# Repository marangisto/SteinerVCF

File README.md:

# SteinerVCF
Steiner VCF Replica

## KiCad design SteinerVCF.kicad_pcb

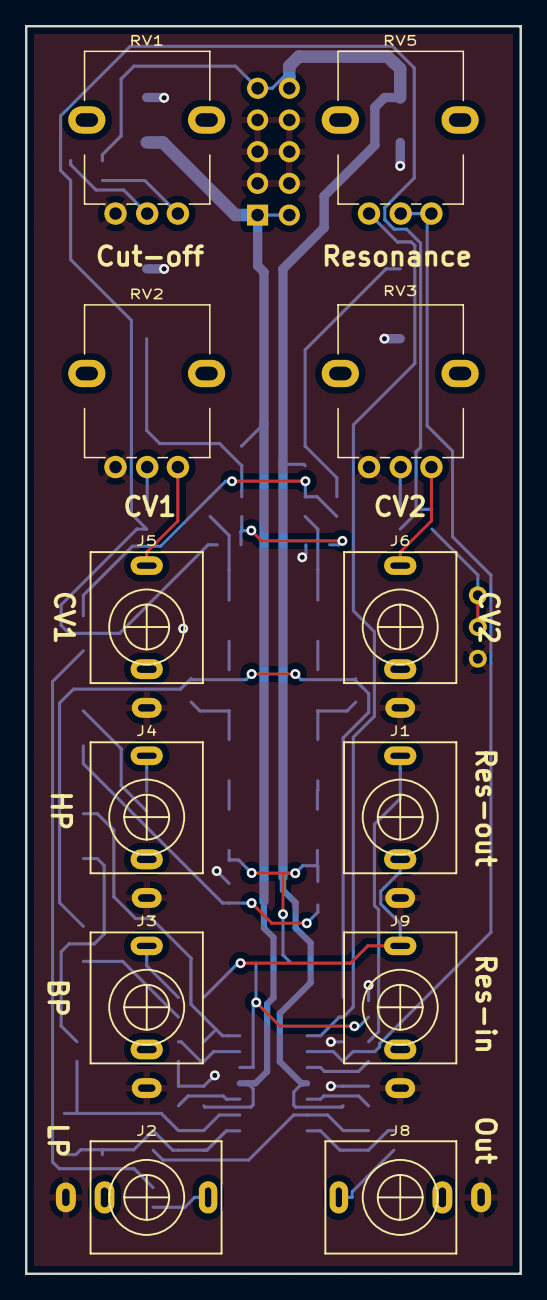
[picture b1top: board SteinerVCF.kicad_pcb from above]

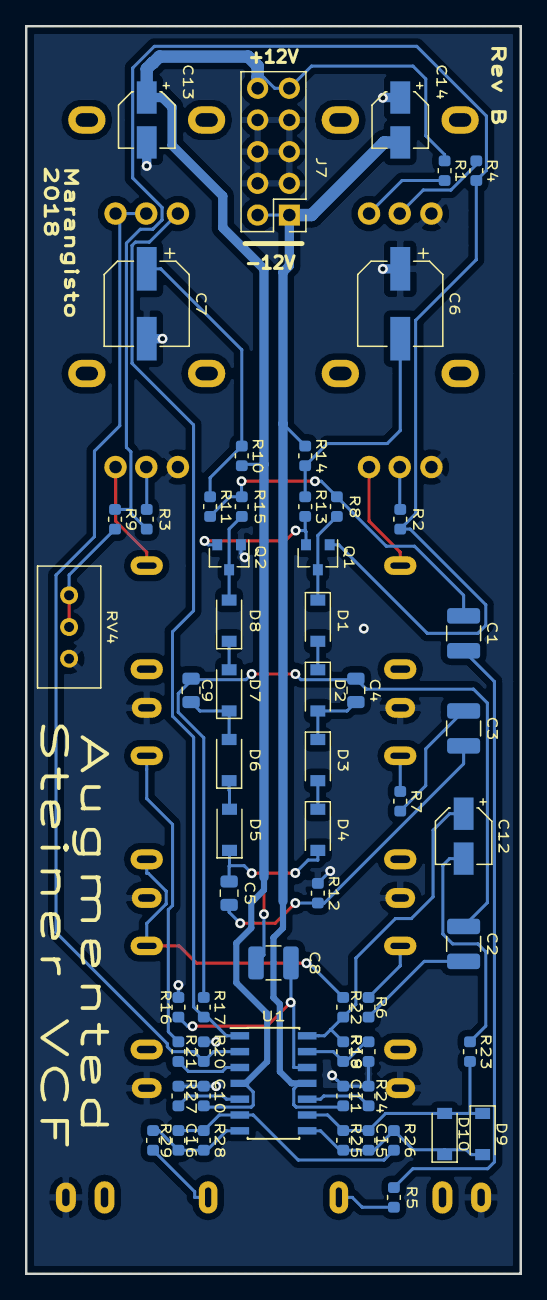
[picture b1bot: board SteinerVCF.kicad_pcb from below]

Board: 2 copper layers, 39.6 x 100.0 mm, 72 parts (60 on the bottom side), 48 nets.

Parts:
C1, C2, C3, C8: 1u; C_1210_3225Metric
C4, C5, C9: 2n2; C_0805_2012Metric
C6, C7: 47u; CP_Elec_6.3x5.4
C10, C11: 100n; C_0603_1608Metric
C12, C13, C14: 10u; CP_Elec_4x5.8
C15, C16: 22p; C_0603_1608Metric
D1, D2, D3, D4, D5, D6, D7, D8, D9, D10: 1N4148W; D_SOD-123
J1, J2, J3, J4, J5, J6, J8, J9: AudioJack2_Ground_Switch; PJ398SM
J7: Conn_02x05_Odd_Even; PinHeader_2x05_P2.54mm_Vertical
Q1, Q2: BC847; SOT-23
R1: 100k; R_0603_1608Metric
R2, R3, R4: 220k; R_0603_1608Metric
R5, R6, R7: 56k; R_0603_1608Metric
R8, R15: 2k2; R_0603_1608Metric
R9: 470; R_0603_1608Metric
R10: 390; R_0603_1608Metric
R11, R12, R17, R22, R29: 1k; R_0603_1608Metric
R13: 3K3; R_0603_1608Metric
R14: 82; R_0603_1608Metric
R16: 2200k; R_0603_1608Metric
R18: 22k; R_0603_1608Metric
R19: 4K7; R_0603_1608Metric
R20, R21: 100K; R_0603_1608Metric
R23, R26, R27: 10k; R_0603_1608Metric
R24: 6k8; R_0603_1608Metric
R25: 33k; R_0603_1608Metric
R28: 150k; R_0603_1608Metric
RV1, RV2, RV3, RV5: 100k; AlpsRK09K
RV4: 2k; Bourns3296WV
U1: TL074; SOIC-14_3.9x8.7mm_P1.27mm

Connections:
+12V: C10.1, C13.1, J7.9, J7.10, R1.2, R10.1, U1.4
-12V: C11.2, C14.2, J7.1, J7.2, R14.2, U1.11
/BP: J3.T, R6.2
/CV1: J5.T, RV2.1
/CV2: J6.T, RV3.1
/CutOff: R4.2, RV1.2
/HP: J4.T, R7.2
/LP: J2.T, R5.2
/Resonance: R20.1, RV5.1, RV5.2, U1.2
GND: C6.1, C7.2, C10.2, C11.1, C13.2, C14.1, J1.S, J2.S, J3.S, J4.S, J5.S, J6.S, J7.3, J7.4, J7.5, J7.6, J7.7, J7.8, J8.S, J9.S, Q2.1, R12.2, R16.2, R18.2, R20.2, R24.2, R27.2, RV1.3, RV2.3, RV3.3, RV4.3
LoopIn: J1.T, R21.1
LoopOut: J1.TN, J9.T, R22.1
unnamed: C1.1, R8.1, R11.1, R15.1
unnamed: C1.2, R5.1
unnamed: C2.1, C4.2, C9.2, R17.2
unnamed: C2.2, R6.1
unnamed: C3.1, C5.2, R12.1
unnamed: C3.2, R7.1
unnamed: C4.1, D2.2, D3.1
unnamed: C5.1, C8.2, D4.2, D5.1
unnamed: C6.2, R13.2, R14.1
unnamed: C7.1, R10.2, R11.2
unnamed: C8.1, R16.1, U1.12
unnamed: C9.1, D6.2, D7.1
unnamed: C12.1, R19.1, R22.2, U1.14
unnamed: C12.2, R23.2
unnamed: C15.1, D9.2, D10.1, R25.1, R26.2, U1.8
unnamed: C15.2, D9.1, D10.2, R23.1, R25.2, U1.9
unnamed: C16.1, R28.1, R29.2, U1.7
unnamed: C16.2, R26.1, R28.2, U1.6
unnamed: D1.1, Q1.3, R8.2
unnamed: D1.2, D2.1
unnamed: D3.2, D4.1
unnamed: D5.2, D6.1
unnamed: D7.2, D8.1
unnamed: D8.2, Q2.3, R15.2
unnamed: J8.T, R29.1
unnamed: Q1.1, R2.2, R3.2, R4.1, R9.1
unnamed: Q1.2, Q2.2, R13.1
unnamed: R1.1, RV1.1
unnamed: R2.1, RV2.2
unnamed: R3.1, RV3.2
unnamed: R9.2, RV4.1, RV4.2
unnamed: R17.1, RV5.3, U1.1
unnamed: R18.1, R19.2, U1.13
unnamed: R21.2, U1.3
unnamed: R24.1, U1.10
unnamed: R27.1, U1.5

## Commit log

2018-10-13 Initial circuit (based on Ken Stone's design).
2018-10-25 Integrated changes from yusynth's schematic.
2018-10-25 Ignore vim swap files.
2018-10-25 Added footprints.
2018-10-28 Early placement.
2018-10-28 Spice model.
2018-11-02 Lots of spicing.
2018-11-02 First reasonable frequency response.
2018-11-02 Simplified and regularized inputs.
2018-11-02 Removed shorted components.
2018-11-02 Ignore raw and log files.
2018-11-03 Treat .asc files as text.
2018-11-03 Resonance to not alter total gain.
2018-11-03 Two-stage output.
2018-11-03 12V version and output low-pass.
2018-11-03 Use 100k pots.
2018-11-03 Use BC847B transistors and some clean-up.
2018-11-03 Prettier layout and comments.
2018-11-03 Moved and balanced clipping circuit.
2018-11-03 Adjusted for unit gain.
2018-11-03 Added frequency response plot.
2018-11-03 Added board layout drawing.
2018-11-03 Added edge-cuts.
2018-11-03 Added panel renderings.
2018-11-03 Second CV input and taps for resonance loop.
2018-11-03 Redesigned schematic based on spice simulation.
2018-11-03 Swap input resistors and caps.
2018-11-03 Initial component placement.
2018-11-03 More placement.
2018-11-04 Full-board placement complete.
2018-11-04 Completed signal routing.
2018-11-04 Ground pours and stiching.
2018-11-04 Better placement of large caps.
2018-11-04 Moved some caps away from the edge.
2018-11-04 Silkscreen orientation.
2018-11-04 Silkscreen branding.
2018-11-04 Added a board image.
2018-11-04 Added BOM.
2018-11-04 Added gerbers.
2018-11-04 Updated silk-screein with power designators.
2018-11-04 Added pcb image.
2018-11-06 Added 3-d model for RK09 potentiometer.
2018-11-06 Added 3-model for PJ398SM.
2018-11-06 Added bourns trimmer 3-d model.
2018-11-06 Added ray-trace renderings.
2018-11-06 Added drafting drawings for 3-d models.
2018-11-06 Modeled threads.
2018-11-11 Freerouted signals.
2019-03-14 Added missing fp-lib-table.
2019-03-14 Added png files for calibration procedure.
